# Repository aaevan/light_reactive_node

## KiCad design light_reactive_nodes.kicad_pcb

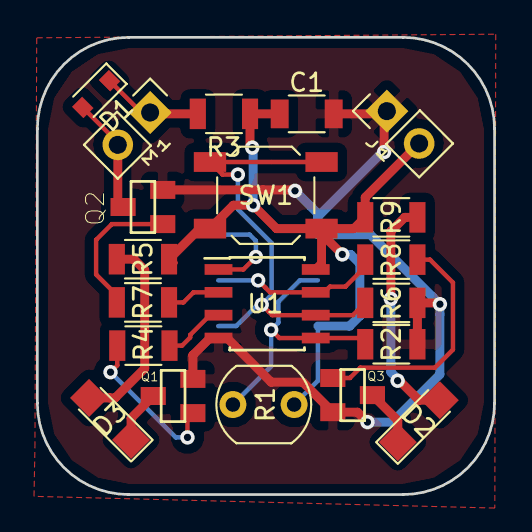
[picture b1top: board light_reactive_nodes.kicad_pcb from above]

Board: 2 copper layers, 25.4 x 25.4 mm, 21 parts (1 on the bottom side), 17 nets.

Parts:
C1: C; C_1206
CON1: AVR-ISP-6; Pin_Header_Straight_2x03_Pitch2.54mm_SMD
D1: DIODE; D_0805
D2, D3: LED; LED_1206
J1: CONN_01X02_FEMALE; Pin_Header_Straight_1x02_Pitch2.54mm
M1: Vibration Motor; Pin_Header_Straight_1x02_Pitch2.54mm
Q1, Q2, Q3: MMBT2222A; SOT23
R1: LDR03; Resistor_LDR_5.1x4.3_RM3.4
R2, R4, R6, R7, R8: 10k; R_1206
R3, R5, R9: 220; R_1206
SW1: SW_DIP_x01; SW_SPST_SKQG
U1: ATTINY85-20SU; SOIC-8_3.9x4.9mm_Pitch1.27mm

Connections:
/MISO: CON1.1, R6.1, SW1.2, U1.6
/MOSI: CON1.4, R1.2, R2.1, U1.5
/PB2: CON1.3, R8.2, U1.7
/PB3: R7.2, U1.2
/PB4: R4.2, U1.3
/RST: CON1.5, U1.1
GND: C1.2, CON1.6, J1.1, Q1.2, Q2.2, Q3.2, R2.2, R6.2, U1.4
unnamed: D1.1, M1.1, R3.2
unnamed: D1.2, M1.2, Q2.3
unnamed: D2.1, Q3.3
unnamed: D2.2, R9.2
unnamed: D3.1, Q1.3
unnamed: D3.2, R5.2
unnamed: Q1.1, R4.1
unnamed: Q2.1, R7.1
unnamed: Q3.1, R8.1
VCC: C1.1, CON1.2, J1.2, R1.1, R3.1, R5.1, R9.1, SW1.1, U1.8
